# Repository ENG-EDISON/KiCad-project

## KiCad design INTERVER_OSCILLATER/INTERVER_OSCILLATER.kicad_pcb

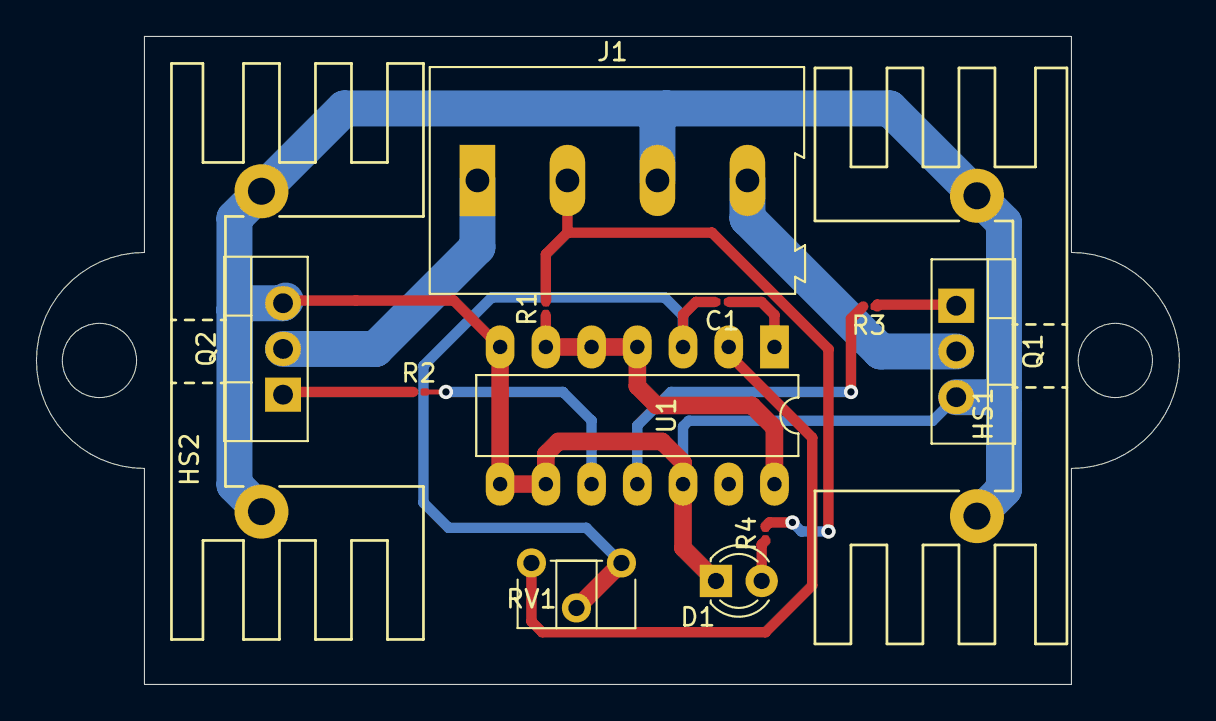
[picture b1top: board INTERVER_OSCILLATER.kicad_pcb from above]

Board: 2 copper layers, 63.5 x 36.0 mm, 13 parts (0 on the bottom side), 13 nets.

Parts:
C1: 104J; C_0201_0603Metric
D1: LED; LED_D3.0mm
HS1, HS2: Heatsink_Pad_3Pin; Heatsink_Stonecold_HS-132_32x14mm_2xFixation1.5mm
J1: Screw_Terminal_01x04; TerminalBlock_Altech_AK300-4_P5.00mm
Q1, Q2: BSB044N08NN3; TO-220-3_Vertical
R1, R2, R3, R4: 10k; R_0201_0603Metric
RV1: 484k; Potentiometer_ACP_CA6-H2,5_Horizontal
U1: 4047; DIP-14_W7.62mm_LongPads

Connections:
/T_SIDE_1: J1.1, Q2.2
/T_SIDE_2: J1.4, Q1.2
GND: D1.1, HS1.1, HS2.1, J1.3, Q1.3, Q2.3, U1.7, U1.8, U1.9, U1.12
unnamed: C1.1, U1.1
unnamed: C1.2, RV1.1, RV1.2, U1.3
unnamed: D1.2, R4.1
unnamed: Q1.1, R3.1
unnamed: Q2.1, R2.1
unnamed: R1.1, U1.4, U1.5, U1.6, U1.14
unnamed: R2.2, U1.10
unnamed: R3.2, U1.11
unnamed: RV1.3, U1.2
VCC: J1.2, R1.2, R4.2

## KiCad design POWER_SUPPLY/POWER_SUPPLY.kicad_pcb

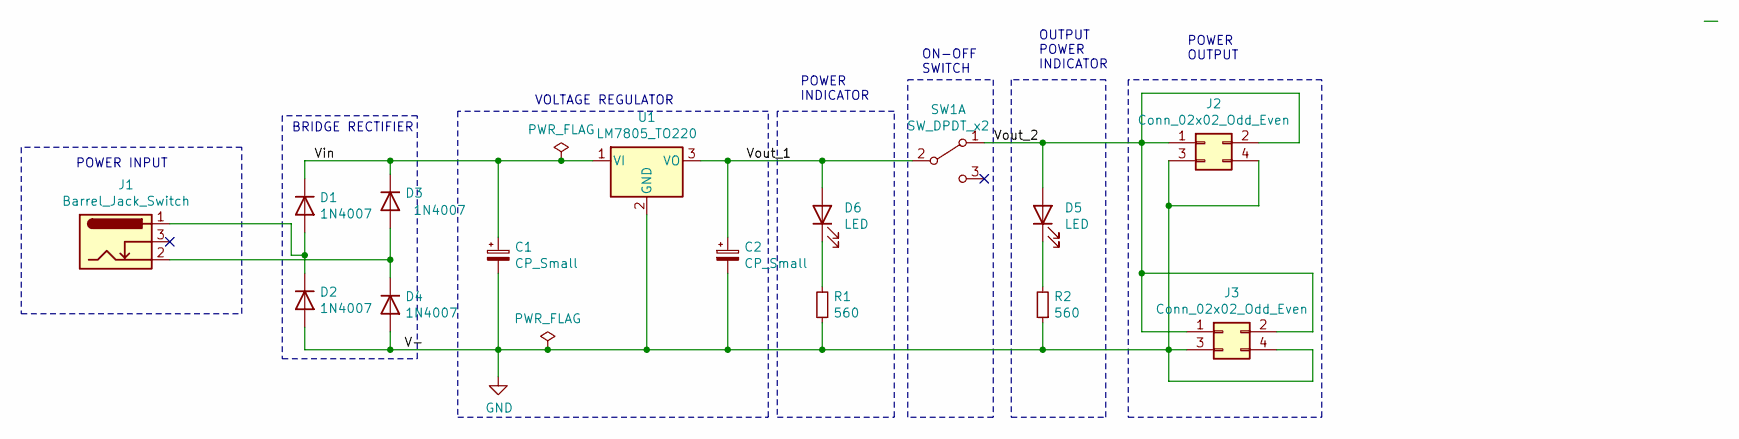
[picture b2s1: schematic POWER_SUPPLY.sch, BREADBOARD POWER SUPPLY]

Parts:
C1: CP_Small; CP_Radial_D10.0mm_P5.00mm
C2: CP_Small; CP_Radial_D6.3mm_P2.50mm
D1, D2, D3, D4: 1N4007; D_DO-41_SOD81_P10.16mm_Horizontal
D5, D6: LED; LED_D5.0mm
J1: Barrel_Jack_Switch; BarrelJack_CUI_PJ-102AH_Horizontal
J2, J3: Conn_02x02_Odd_Even; PinHeader_2x02_P2.54mm_Vertical
R1, R2: 560; R_Axial_DIN0207_L6.3mm_D2.5mm_P10.16mm_Horizontal
SW1: SW_DPDT_x2; Switch_Slide_11.6x4mm_EG1218
U1: LM7805_TO220; TO-220-3_Vertical

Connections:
/Vin: C1.1, D1.1 (K), D3.1 (K), U1.1 (VI)
/Vout_1: C2.1, D6.2 (A), SW1.2 (B), U1.3 (VO)
/Vout_2: D5.2 (A), J2.1, J2.2, J3.1, J3.2, SW1.1 (A)
GND: C1.2, C2.2, D2.2 (A), D4.2 (A), J2.3, J2.4, J3.3, J3.4, R1.1, R2.1, U1.2 (GND)
unnamed: D1.2 (A), D2.1 (K), J1.1
unnamed: D3.2 (A), D4.1 (K), J1.2
unnamed: D5.1 (K), R2.2
unnamed: D6.1 (K), R1.2

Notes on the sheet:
POWER INPUT
BRIDGE RECTIFIER
VOLTAGE REGULATOR
POWER INDICATOR
ON-OFF SWITCH
OUTPUT POWER INDICATOR
POWER OUTPUT

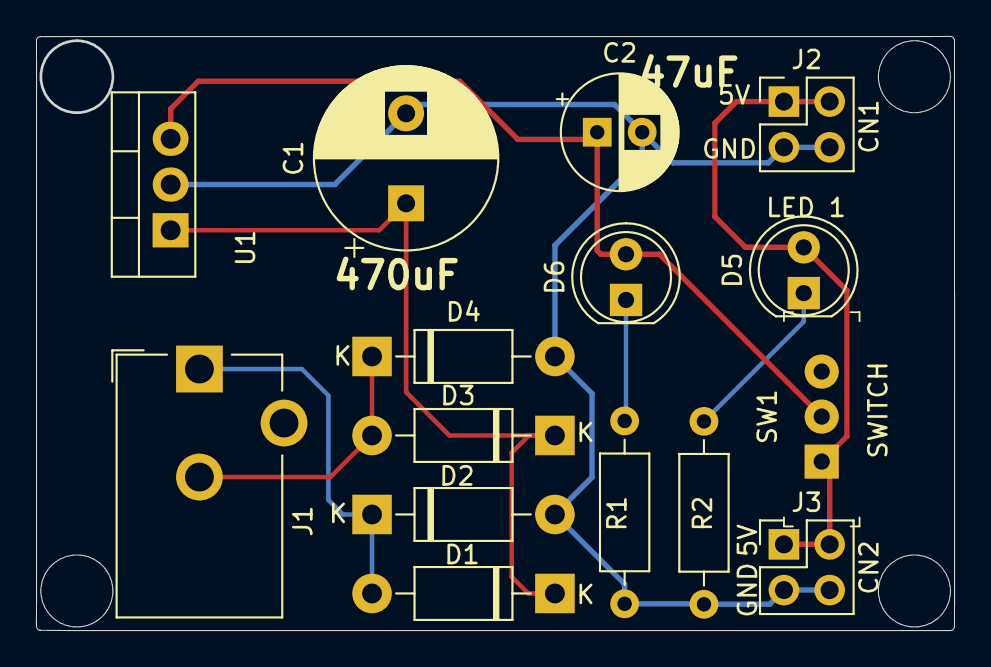
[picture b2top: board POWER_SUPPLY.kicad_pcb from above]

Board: 2 copper layers, 50.9 x 32.9 mm, 15 parts (0 on the bottom side), 8 nets.

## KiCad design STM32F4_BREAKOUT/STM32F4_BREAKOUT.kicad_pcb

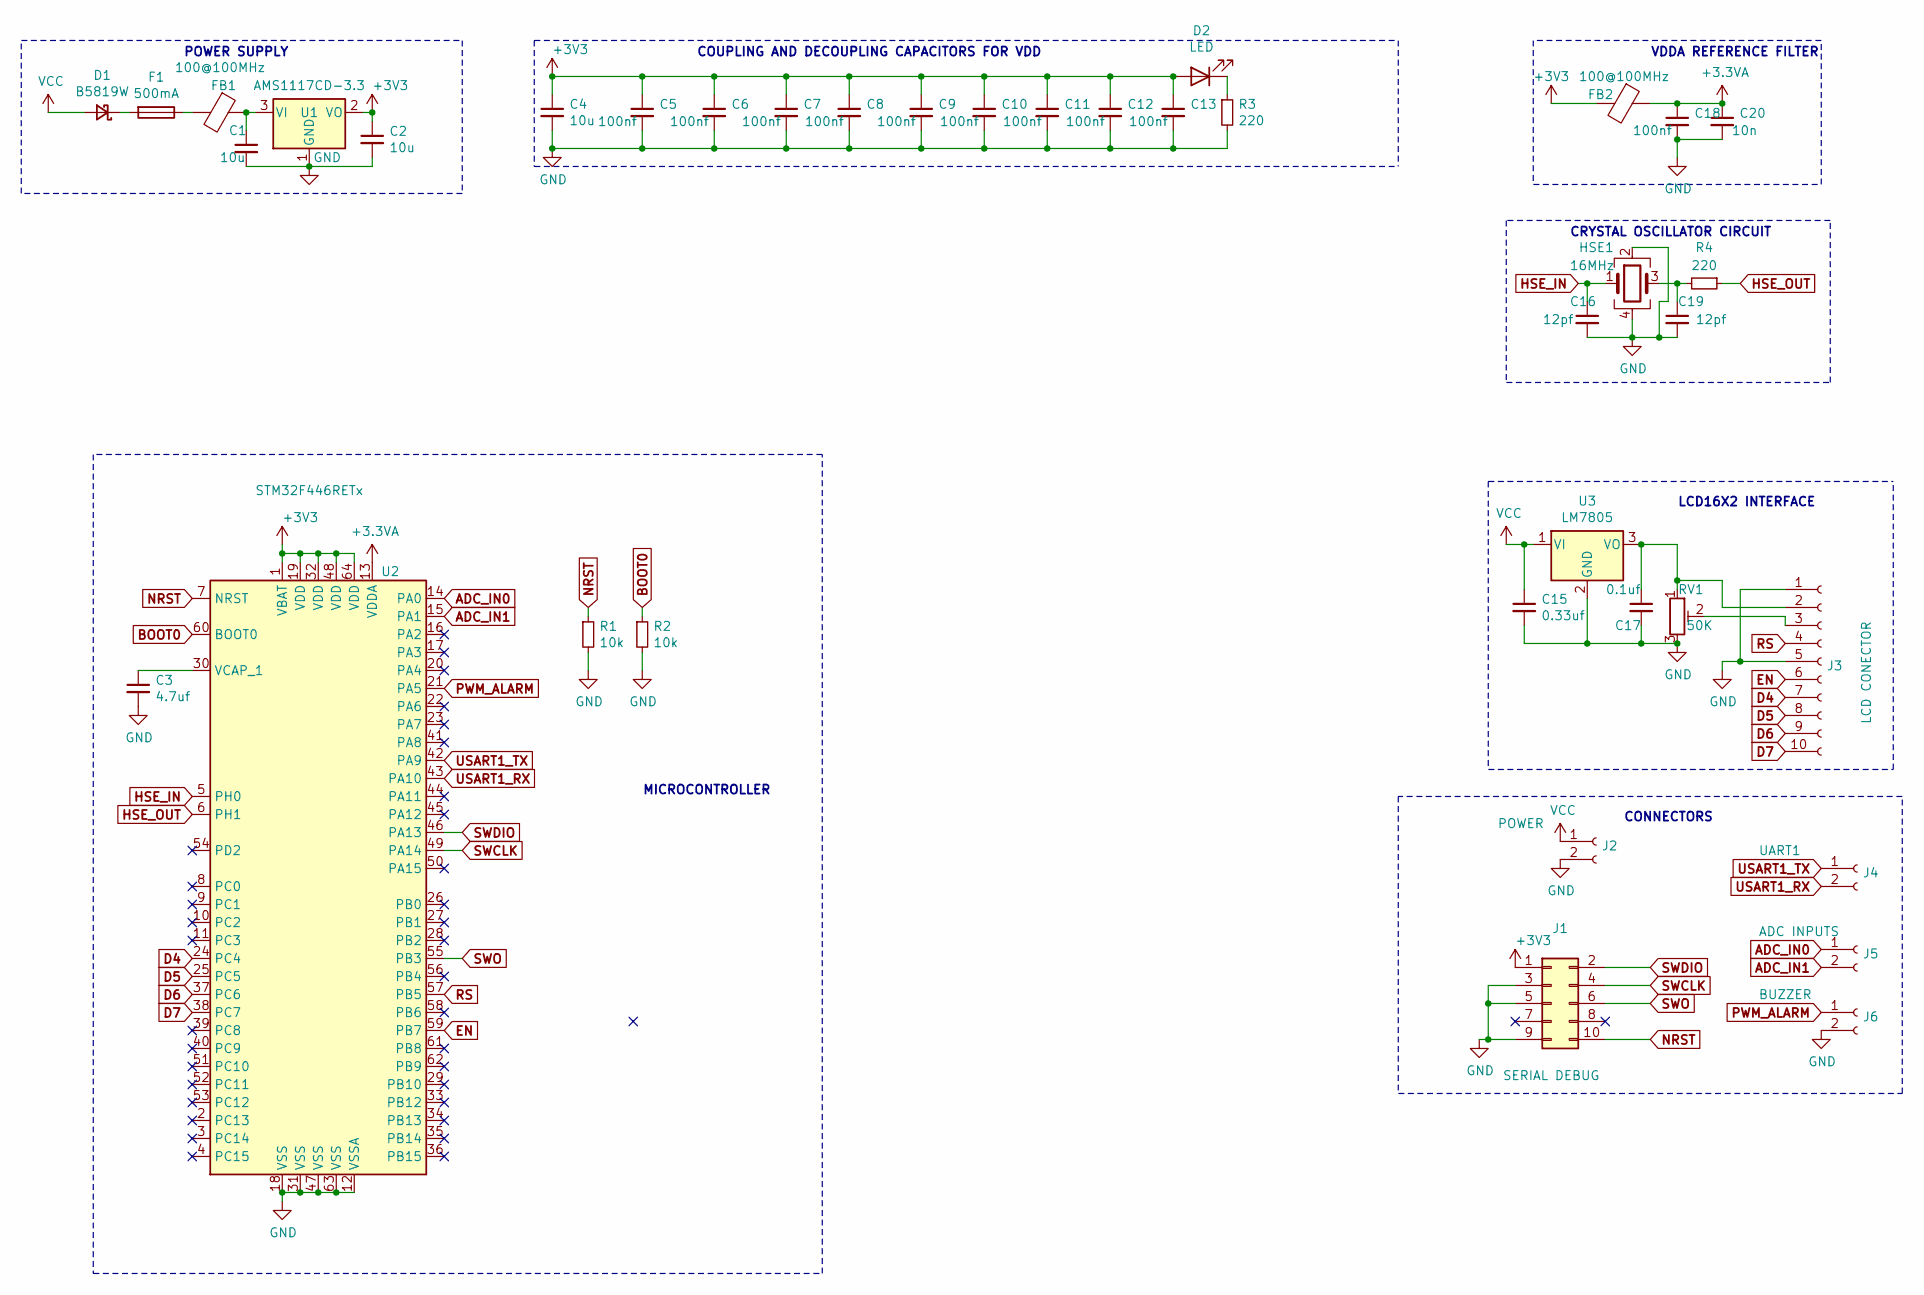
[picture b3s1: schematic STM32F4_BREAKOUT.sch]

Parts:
C1, C2, C4: 10u; C_0805_2012Metric
C3: 4.7uf; C_0805_2012Metric
C5, C6, C7, C8, C9, C10, C11, C12, C13, C18: 100nf; C_0402_1005Metric
C15: 0.33uf; C_Elec_4x5.4
C16, C19: 12pf; C_0402_1005Metric
C17: 0.1uf; C_0402_1005Metric
C20: 10n; C_0805_2012Metric
D1: B5819W; D_SOD-123
D2: LED; LED_0603_1608Metric
F1: 500mA; Fuse_0603_1608Metric
FB1, FB2: 100@100MHz; L_0805_2012Metric
HSE1: 16MHz; Crystal_SMD_3225-4Pin_3.2x2.5mm
J1: SERIAL DEBUG; PinHeader_2x05_P2.54mm_Vertical
J2: POWER; PinHeader_2x01_P2.00mm_Vertical
J3: LCD CONECTOR; PinHeader_2x05_P2.54mm_Vertical
J4: UART1; PinHeader_1x02_P2.54mm_Vertical
J5: ADC INPUTS; PinHeader_1x02_P2.54mm_Vertical
J6: BUZZER; PinHeader_1x02_P2.54mm_Vertical
R1, R2: 10k; R_0402_1005Metric
R3, R4: 220; R_0402_1005Metric
RV1: 50K; Potentiometer_Vishay_T73XW_Horizontal
U1: AMS1117CD-3.3; SOT-223-3_TabPin2
U2: STM32F446RETx; LQFP-64_10x10mm_P0.5mm
U3: LM7805; TO-263-3_TabPin2

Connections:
+3.3VA: C18.1, C20.1, FB2.1, U2.13 (VDDA)
+3V3: C2.1, C4.1, C5.1, C6.1, C7.1, C8.1, C9.1, C10.1, C11.1, C12.1, C13.1, D2.2 (A), FB2.2, J1.1, U1.2 (VO), U2.1 (VBAT), U2.19 (VDD), U2.32 (VDD), U2.48 (VDD), U2.64 (VDD); also elsewhere on the board
ADC_IN0: J5.1, U2.14 (PA0)
ADC_IN1: J5.2, U2.15 (PA1)
BOOT0: R2.1, U2.60 (BOOT0)
D4: J3.7, U2.24 (PC4)
D5: J3.8, U2.25 (PC5)
D6: J3.9, U2.37 (PC6)
D7: J3.10, U2.38 (PC7)
EN: J3.6, U2.59 (PB7)
GND: C1.2, C2.2, C3.2, C4.2, C5.2, C6.2, C7.2, C8.2, C9.2, C10.2, C11.2, C12.2, C13.2, C15.2, C16.2, C17.2, C18.2, C19.2, C20.2, HSE1.2, HSE1.4, J1.3, J1.5, J1.9, J2.2, J3.1, J3.5, J6.2, R1.2, R2.2, R3.2, RV1.3, U1.1 (GND), U2.12 (VSSA), U2.18 (VSS), U2.31 (VSS), U2.47 (VSS), U2.63 (VSS), U3.2 (GND); also elsewhere on the board
HSE_IN: C16.1, HSE1.1, U2.5 (PH0)
HSE_OUT: R4.1, U2.6 (PH1)
NRST: J1.10, R1.1, U2.7 (NRST)
unnamed: C1.1, FB1.1, U1.3 (VI)
unnamed: C3.1, U2.30 (VCAP_1)
unnamed: C17.1, J3.2, RV1.1, U3.3 (VO)
unnamed: C19.1, HSE1.3, R4.2
unnamed: D1.1 (K), F1.2
unnamed: D2.1 (K), R3.1
unnamed: F1.1, FB1.2
unnamed: J3.3, RV1.2
PWM_ALARM: J6.1, U2.21 (PA5)
RS: J3.4, U2.57 (PB5)
SWCLK: J1.4, U2.49 (PA14)
SWDIO: J1.2, U2.46 (PA13)
SWO: J1.6, U2.55 (PB3)
USART1_RX: J4.2, U2.43 (PA10)
USART1_TX: J4.1, U2.42 (PA9)
VCC: C15.1, D1.2 (A), J2.1, U3.1 (VI)

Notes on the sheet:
POWER SUPPLY
CRYSTAL OSCILLATOR CIRCUIT
COUPLING AND DECOUPLING CAPACITORS FOR VDD
VDDA REFERENCE FILTER
LCD16X2 INTERFACE
CONNECTORS
MICROCONTROLLER

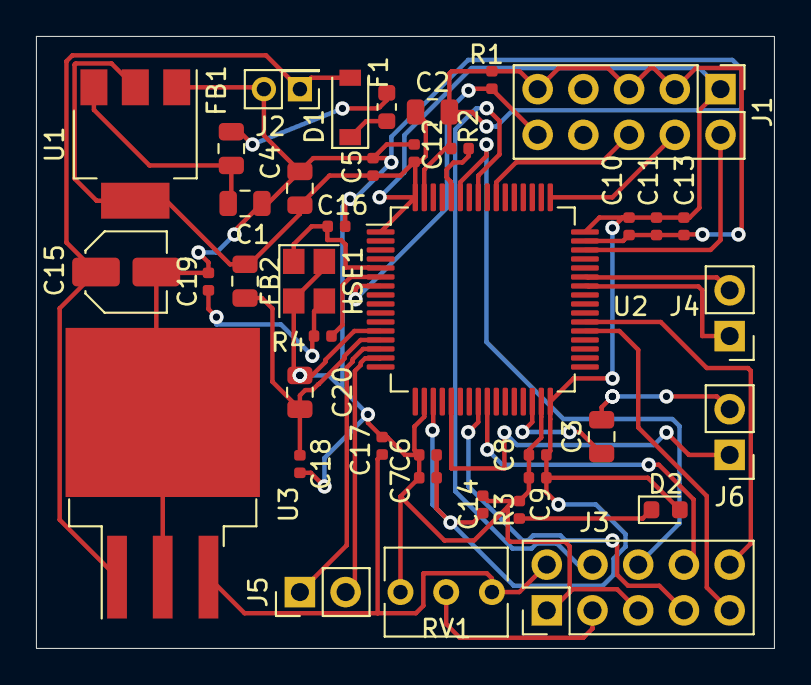
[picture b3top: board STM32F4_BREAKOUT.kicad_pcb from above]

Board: 2 copper layers, 41.0 x 34.0 mm, 40 parts (0 on the bottom side), 30 nets.

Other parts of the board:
C14: 100nf; C_0402_1005Metric

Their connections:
+3V3: C14.1; also elsewhere on the board
GND: C14.2; also elsewhere on the board

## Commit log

2021-08-29 STM32F446RE Break out Board
    This design has LCD and ADC port for adc measuremtents and display
2021-10-30 Power supply
    Power supply of 5v
2021-10-30 Inverter oscillator
    Inverter oscillator circuit
2025-08-22 added Runtime testor project
